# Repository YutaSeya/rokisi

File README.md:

# ロボトレーサー(仮名称ロキシ)

ロボトレース競技に参加するために製作したロボットの機体の設計データ、サンプルプログラムのリポジトリです。

仮名称のロキシは、ロボトレの基本を学ぶ車体の頭文字をとったものです。

## リポジトリの概要

このリポジトリのディレクトリ構成は以下のようになっています。

- Hardware
  - kicadのデータ等
  - 機械設計のデータ等
- firmware
  - Inc
  - Src
  - makefile
  - .gitignore
- LICENSE

# firmwareの使用方法について
1.makeやarm_none_eabi_gccのtoolchain等をインストールする。

Windows環境の開発環境の構築例: [PCの開発環境を整える(Windows10 WSL)](https://garberas.com/archives/38)

2. gitを使用してこのリポジトリをクローンする。
```bash
$git clone  
$cd 
```
3. このリポジトリのビルドを行う
```bash
$cd firmware/  
$make
```

初期プログラムでは、初期化関数だけ実行されます。Lチカを一度行い無限ループでなんの処理も行われません。
周辺機能を使用する時は、ファイルを確認していただければと思います。
また、モーターの回転方向等については、一意に決定することのできないため各自で書き換えていただければと思います。
該当する関数は、controlMotorです。

# hardwareについて
ハードウェアのファイルはkicadの回路設計データとモーターマウント等のSTL形式データが入っています。

使用しているモーターはドローンモーターのφ8.5mm,長さ20mmの8520モーター(7.4V)、ピニオンギアはkkpmoで購入した歯数20、モジュール0.3、穴径1.0mm、
スパーギアはMisumiのメカニカル加工部品の歯数80、モジュール0.3、穴径18.0mmです。

また、3DプリントデータはDMM.makeのアクリル(ウルトラ)で頼みました。AGILISTAを使用してみることを検討してもいいかもです。
MJFを頼みましたが、磁気式エンコーダを使うには精度が厳しいように感じました。

また、回路図、ハードウェアに複数問題点が見つかっているため、現在訂正中です。適宜データを最新版にアップしていく予定です。よろしくお願いいたします。

# その他
このリポジトリにはST MicroのLLAPIのソースコードが含まれています。

このリポジトリによって生じた問題等に責任は一切負いません。

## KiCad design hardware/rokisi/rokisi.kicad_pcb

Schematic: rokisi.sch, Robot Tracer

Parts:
C1, C3, C5, C15, C18: 10u; C_0603_HandSoldering
C2, C8, C10, C12, C17, C19, C20, C21, C22, C23, C24: 0.1u; C_0603_HandSoldering
C4, C6: 22u; C_0603_HandSoldering
C7: 100u; C_1206_HandSoldering
C9: 2.2u; C_0603_HandSoldering
C11: 1u; C_0603_HandSoldering
C13, C14: 100n; C_0603_HandSoldering
C16: 2.2uf; C_0603_HandSoldering
CN1: CONNECT; Pin_Header_Straight_1x02_Pitch2.54mm
CN2, CN3: CONNECT; Pin_Header_Straight_1x02_Pitch2.00mm
D1: LED; LED_0603_HandSoldering
D2: LATBT66B
D3, D4, D5, D6: LED; LED_0603_HandSoldering_silk
J1, J3, J6, J9: Conn_01x02_Female; enckiban_robotore_pad2
J2, J5, J7, J10: Conn_01x04_Female; enckiban_pad4
J4: Conn_01x13_Female; FFC-SMD_13P-P0.50_X05B20U13T
J8, J11: Conn_01x04_Female; Pin_Header_Straight_1x04_Pitch2.00mm
J12: Conn_01x03_Female; Pin_Header_Straight_1x03_Pitch2.54mm
Q1: SI2323DDS; SOT-23_Handsoldering
R2, R3, R8, R9, R12: 10k; R_0603_HandSoldering
R4, R5: 3.3k; R_0603_HandSoldering
R10, R11, R13, R14, R15, R16, R17: 1k; R_0603_HandSoldering
SW1: Tactsw; B3U-1000P
SW2, SW3: Tactsw; SKRPACE010
U1: SW_SPST; PCM12SMTR
U2: AZ1117-5.0; SOT-223
U3: AZ1086H-3.3; SOT-223
U4: CSTCE20M0V51-R0; CSTCE12M0G52A-R0_HandSolding
U7: tb6612; SSOP-24_5.3x8.2mm_Pitch0.65mm
U8: STM32F405RGT; LQFP-64_10x10mm_Pitch0.5mm
U9, U10: MA700; QFN-16_3x3mm_Pitch0.5mm
U11: MPU-6500; QFN-24_3x3mm_Pitch0.4mm_silk
U12: L3GD20

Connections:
+3V3: C1.2, C2.2, C6.1, C7.1, C8.2, C11.1, C12.1, C17.1, C19.2, C20.2, C22.1, C23.1, C24.2, D2.2, D3.2, D4.2, D5.2, D6.2, J4.1, J6.1, J8.1, J9.1, J11.1, SW2.1, SW3.1, U3.2, U3.4, U7.19, U7.20, U8.1, U8.13, U8.19, U8.32, U8.48, U8.64, U11.8, U11.13, U12.1
+5V: C4.1, C5.1, U2.2 (VO), U2.4, U3.3
+12V: C3.1, Q1.3 (D), R3.1, R4.1, U2.3 (VI), U7.13, U7.14, U7.24
AD0: J4.4, U8.26
AD1: J4.5, U8.25
AD2: J4.6, U8.24
AD3: J4.7, U8.23
AD4: J4.8, U8.22
AD5: J4.9, U8.21
AD6: J4.10, U8.20
AD7: J4.11, U8.17
AD8: J4.12, U8.16
AD9: J4.13, U8.15
AO1: CN2.1, U7.1, U7.2
AO2: CN2.2, U7.5, U7.6
BO1: CN3.1, U7.11, U7.12
BO2: CN3.2, U7.7, U7.8
GND: C1.1, C2.1, C3.2, C4.2, C5.2, C6.2, C7.2, C8.1, C9.1, C10.1, C11.2, C12.2, C16.2, C17.2, C19.1, C20.1, C21.2, C22.2, C23.2, C24.1, CN1.2, D1.1, J4.2, J4.3, J6.2, J8.2, J9.2, J11.2, J12.1, R5.2, R8.2, R9.1, R12.1, SW1.2, U1.2, U2.1 (GND), U3.1, U4.2, U7.3, U7.4, U7.9, U7.10, U7.18, U8.12, U8.18, U8.63, U11.11, U11.18, U11.20, U12.8
LEFT_CS: J2.1, U10.5
LEFT_GND: C14.2, C18.1, J1.2, U10.8
LEFT_MISO: J2.3, U10.7
LEFT_MOSI: J2.4, U10.4
LEFT_SCLK: J2.2, U10.12
LEFT_VDD: C14.1, J1.1, U10.13
unnamed: C9.2, U8.47
unnamed: C10.2, SW1.1, U8.7
unnamed: C15.2, U9.16
unnamed: C16.1, U8.31
unnamed: C18.2, U10.16
unnamed: C21.1, U11.10
unnamed: CN1.1, Q1.2 (S), R2.2
unnamed: D1.2, R4.2
unnamed: D2.1, R10.2
unnamed: D2.3, R11.1
unnamed: D2.4, R13.2
unnamed: D3.1, R14.1
unnamed: D4.1, R15.1
unnamed: D5.1, R16.1
unnamed: D6.1, R17.1
unnamed: Q1.1 (G), R2.1, U1.1
unnamed: R8.1, U8.28
unnamed: U4.1, U8.5
unnamed: U4.3, U8.6
RIGHT_CS: J5.1, U9.5
RIGHT_GND: C13.2, C15.1, J3.2, U9.8
RIGHT_MISO: J5.3, U9.7
RIGHT_MOSI: J5.4, U9.4
RIGHT_SCLK: J5.2, U9.12
RIGHT_VDD: C13.1, J3.1, U9.13
ad11: J8.3, U8.27
ad12: J11.3, U8.14
ain1: U7.21, U8.3
ain2: U7.22, U8.2
batt_analog: R3.2, R5.1, U8.9
bin1: U7.17, U8.4
bin2: U7.16, U8.8
boot: R12.2, SW3.2, U8.59, U8.60
fled_blue: R11.2, U8.44
fled_green: R13.1, U8.45
fled_red: R10.1, U8.46
gyro_clk: U8.51, U11.23, U12.2
gyro_miso: U8.52, U11.9, U12.4
gyro_mosi: U8.53, U11.24, U12.3
l3gd20_cs: U8.10, U12.5
led1: R14.2, U8.37
led2: R16.2, U8.38
led3: R15.2, U8.39
led4: R17.2, U8.40
led_left: J8.4, U8.41
led_right: J11.4, U8.29
mpu_cs: U8.11, U11.22
pushsw1: R9.2, SW2.2, U8.30
pwma: U7.23, U8.61
pwmb: U7.15, U8.62
spi1_clk: J7.2, U8.55
spi1_cs: J7.1, U8.54
spi1_miso: J7.3, U8.56
spi1_mosi: J7.4, U8.57
spi2_clk: J10.2, U8.34
spi2_cs: J10.1, U8.33
spi2_miso: J10.3, U8.35
spi2_mosi: J10.4, U8.36
usart1_rx: J12.2, U8.43
usart1_tx: J12.3, U8.42

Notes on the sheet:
Power
Gyro Sensor
PchMOSFET 20V5A
3-terminal regulator Input 6.25 to 20V OUTPUT 5V1A
3-terminal regulator Input 4.6 to 15V OUTPUT 3.3V1.5A
Motor Driver & Current IC
Encoder
MCU STM32F405RGT 64Pin
User Interface
Sensor Connect

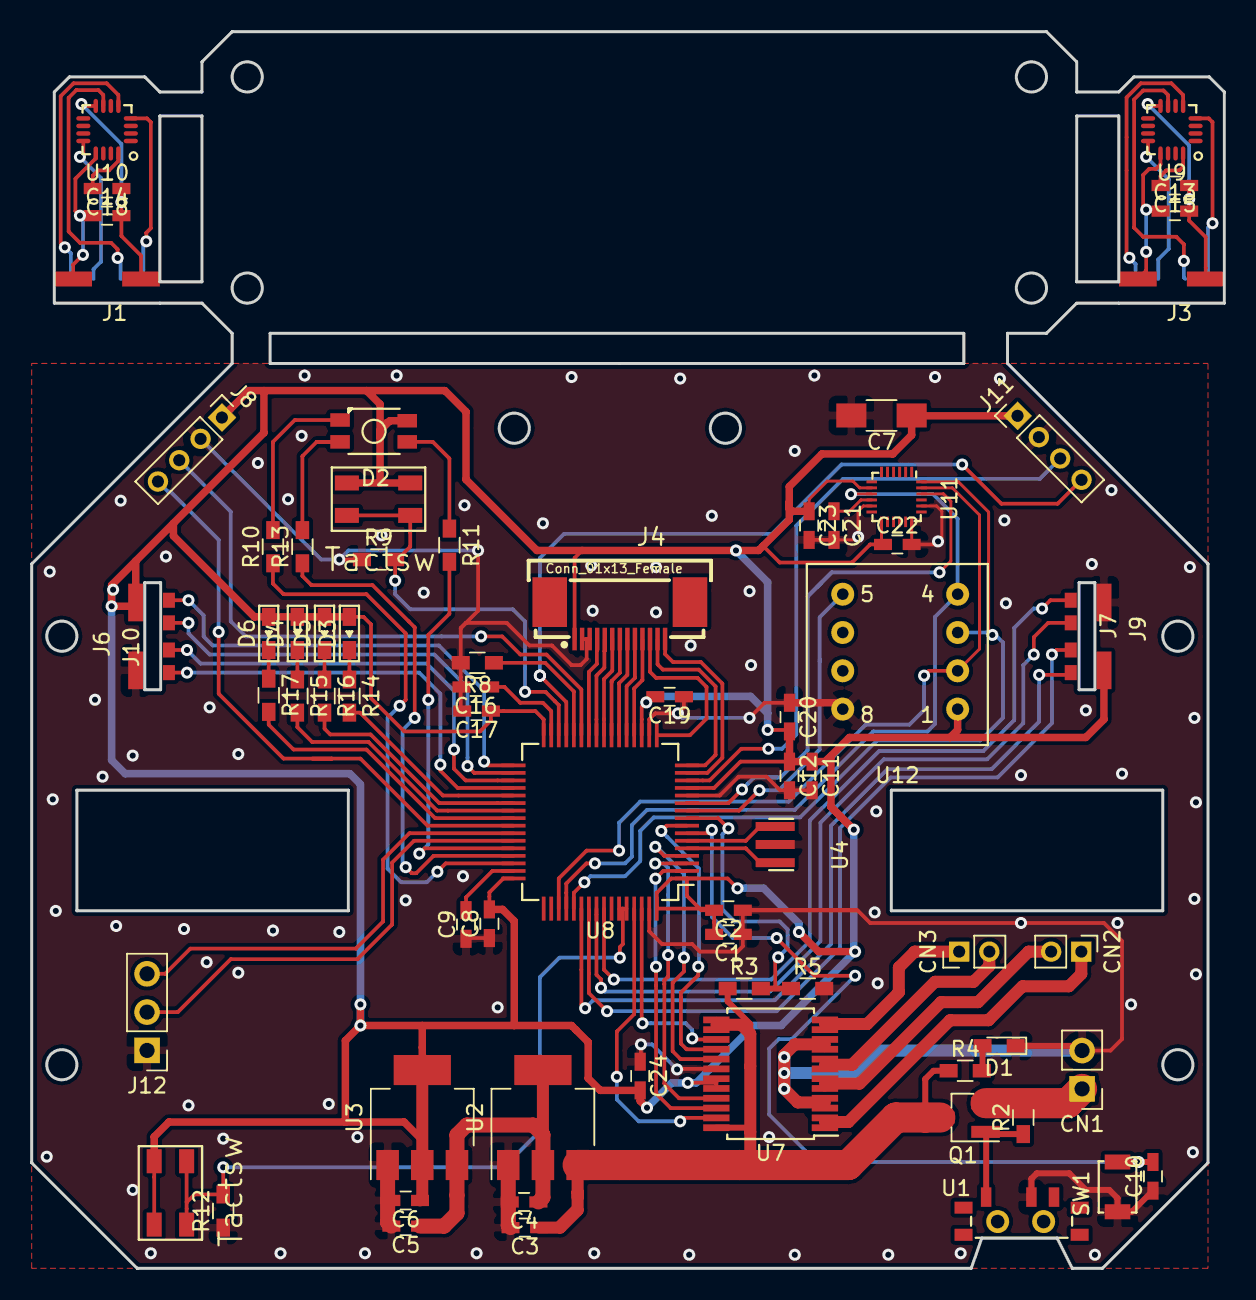
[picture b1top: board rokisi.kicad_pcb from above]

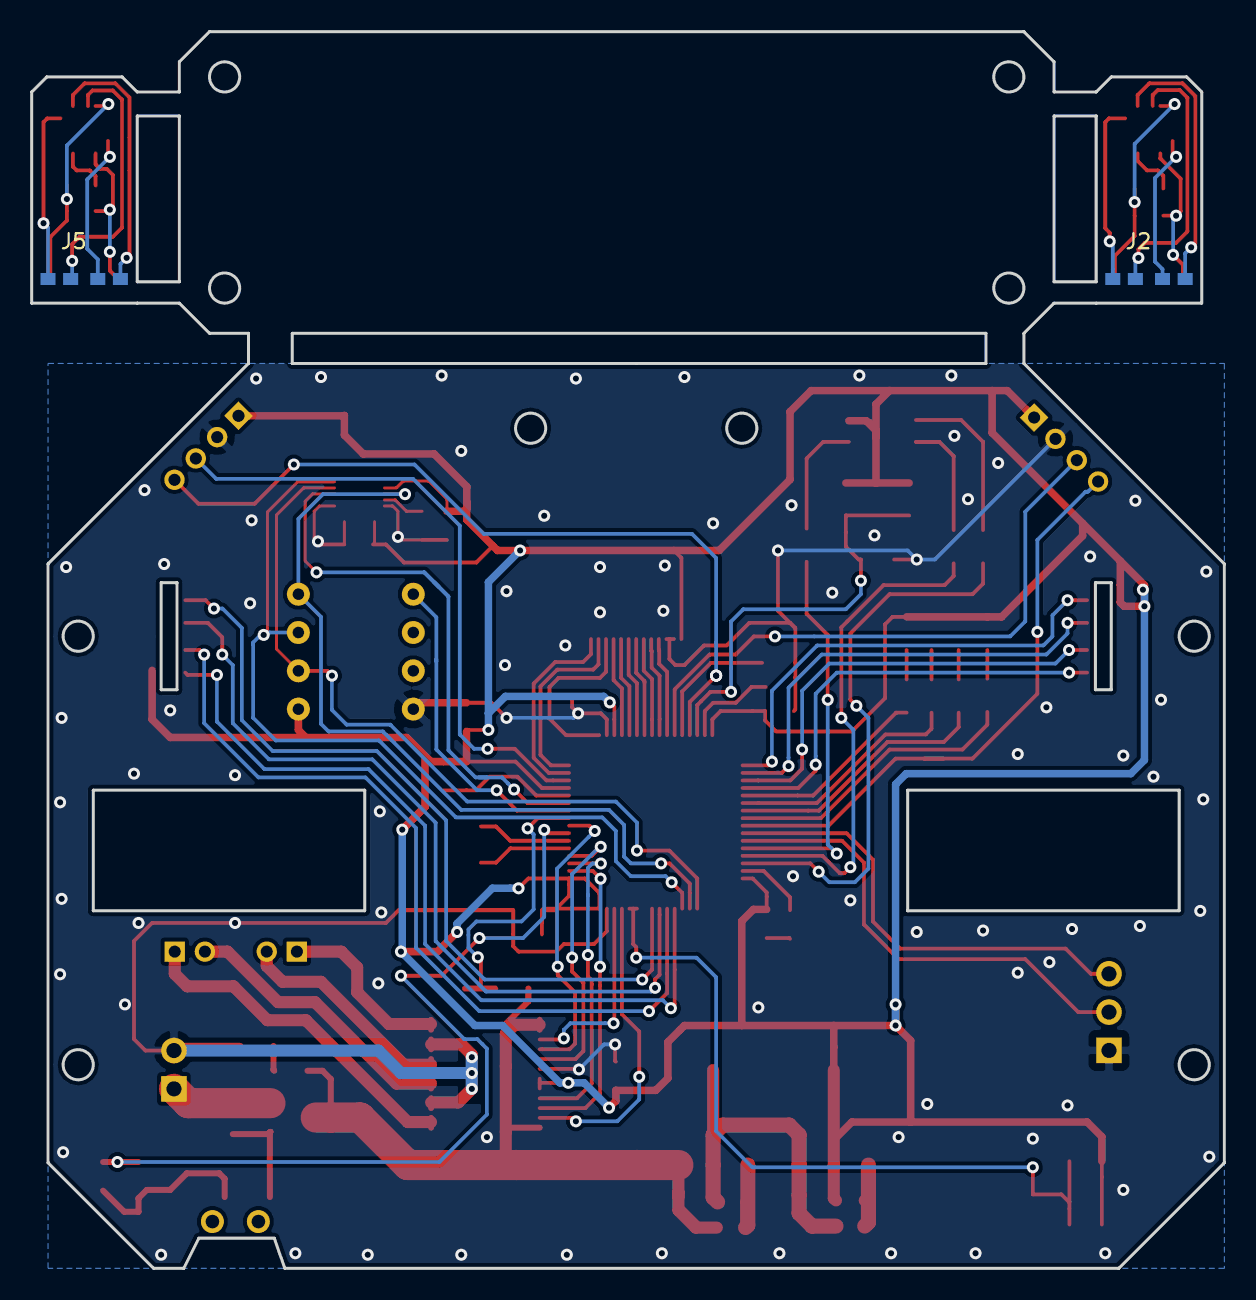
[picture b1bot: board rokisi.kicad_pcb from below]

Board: 2 copper layers, 79.1 x 82.0 mm, 73 parts (2 on the bottom side), 84 nets.

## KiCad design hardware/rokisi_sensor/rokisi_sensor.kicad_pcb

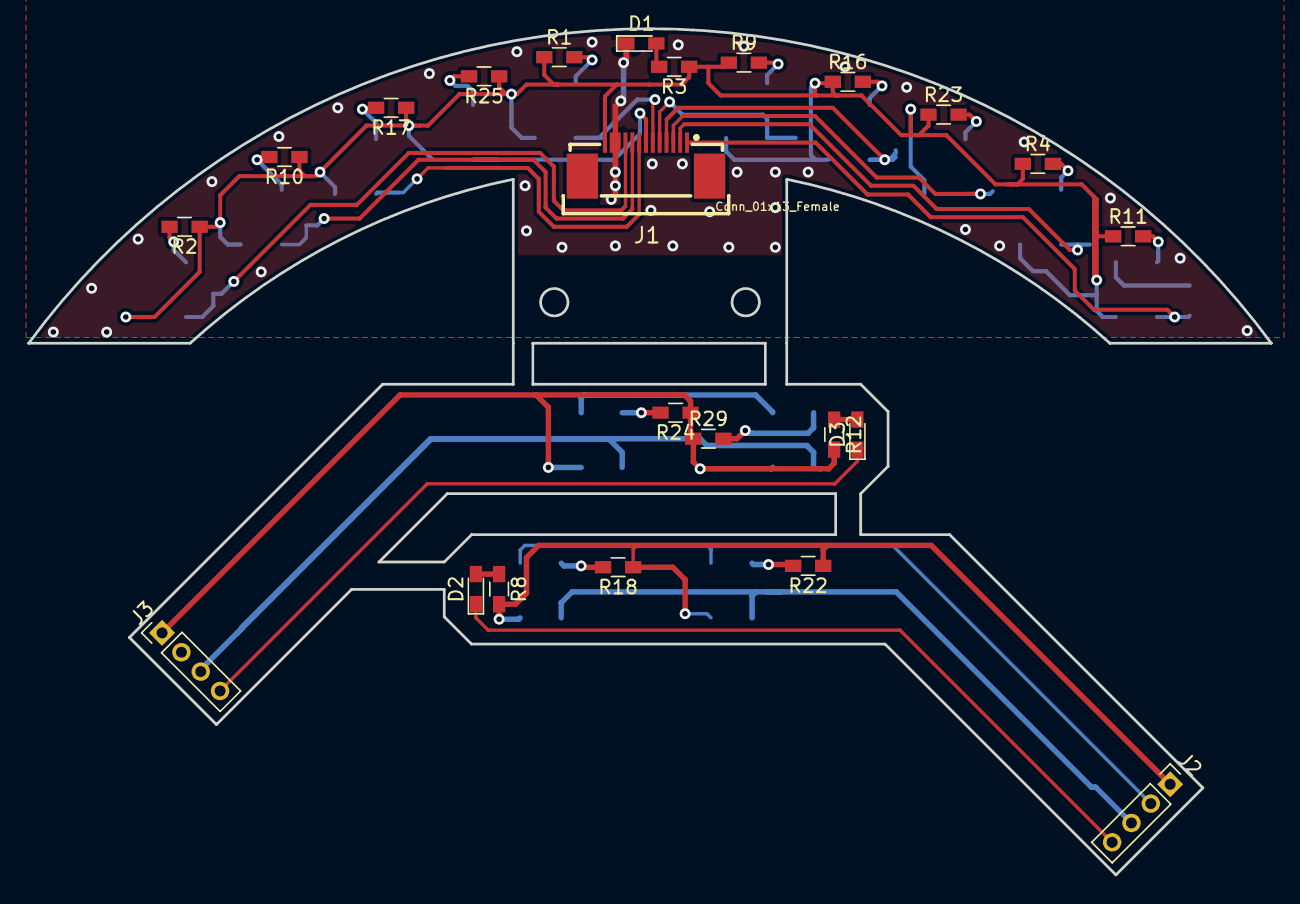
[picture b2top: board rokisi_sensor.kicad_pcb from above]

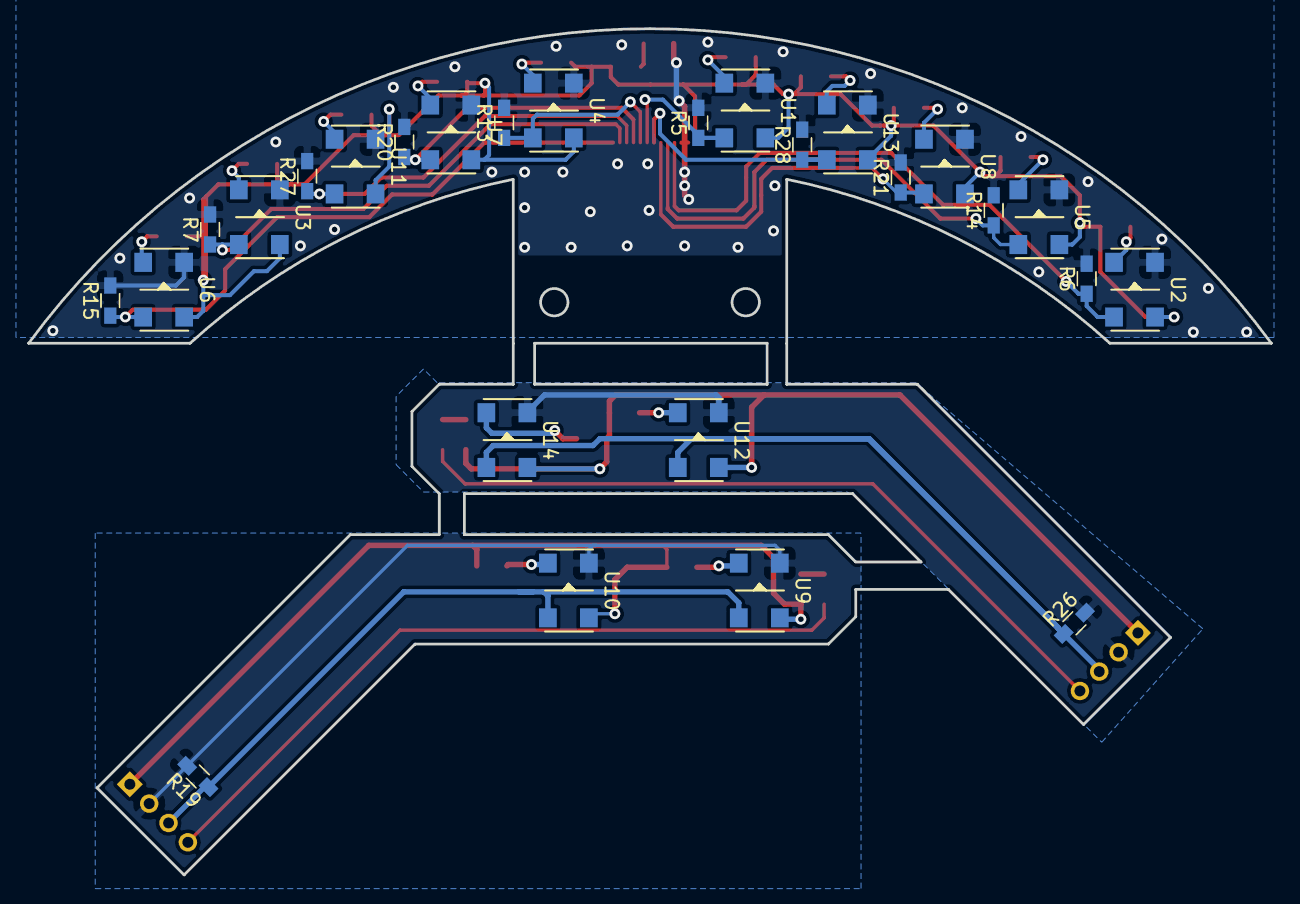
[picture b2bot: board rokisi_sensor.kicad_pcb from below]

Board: 2 copper layers, 90.9 x 61.9 mm, 49 parts (26 on the bottom side), 37 nets.

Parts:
D1, D2, D3: LED; LED_0603_HandSoldering
J1: Conn_01x13_Female; FFC-SMD_13P-P0.50_X05B20U13T
J2, J3: Conn_01x04_Female; Pin_Header_Straight_1x04_Pitch2.00mm
R1, R2, R4, R9, R10, R11, R16, R17, R18, R22, R23, R24, R25, R29: 330; R_0603_HandSoldering
R3, R5, R6, R7, R8, R12, R13, R14, R15, R19, R20, R21, R26, R27, R28: 1k; R_0603_HandSoldering
U1, U2, U3, U4, U5, U6, U7, U8, U9, U10, U11, U12, U13, U14: GP2S700HCP

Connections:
+3V3: J1.13, R1.1, R2.1, R3.1, R4.1, R9.1, R10.1, R11.1, R16.1, R17.1, R23.1, R25.1, U1.2, U2.2, U3.2, U4.2, U5.2, U6.2, U7.2, U8.2, U11.2, U13.2
AD0: J1.10, R6.1, U2.1
AD1: J1.9, R14.1, U5.1
AD2: J1.8, R21.1, U8.1
AD3: J1.7, R28.1, U13.1
AD4: J1.6, R5.1, U1.1
AD5: J1.5, R13.1, U4.1
AD6: J1.4, R20.1, U7.1
AD7: J1.3, R27.1, U11.1
AD8: J1.2, R7.1, U3.1
AD9: J1.1, R15.1, U6.1
GND: D1.1, J1.11, J1.12, R5.2, R6.2, R7.2, R13.2, R14.2, R15.2, R20.2, R21.2, R27.2, R28.2, U1.3, U2.3, U3.3, U4.3, U5.3, U6.3, U7.3, U8.3, U11.3, U13.3
LEFT_GND: J2.2, R19.2, U9.3, U10.3
LEFT_VCC: J2.1, R8.2, R18.1, R22.1, U9.2, U10.2
unnamed: D1.2, R3.2
unnamed: D2.2, R8.1
unnamed: D3.2, R12.1
unnamed: R1.2, U1.4
unnamed: R2.2, U2.4
unnamed: R4.2, U3.4
unnamed: R9.2, U4.4
unnamed: R10.2, U5.4
unnamed: R11.2, U6.4
unnamed: R16.2, U7.4
unnamed: R17.2, U8.4
unnamed: R18.2, U9.4
unnamed: R22.2, U10.4
unnamed: R23.2, U11.4
unnamed: R24.2, U12.4
unnamed: R25.2, U13.4
unnamed: R29.2, U14.4
RIGHT_GND: J3.2, R26.2, U12.3, U14.3
RIGHT_VCC: J3.1, R12.2, R24.1, R29.1, U12.2, U14.2
left_analog: J2.3, R19.1, U9.1, U10.1
left_led: D2.1, J2.4
right_analog: J3.3, R26.1, U12.1, U14.1
right_led: D3.1, J3.4

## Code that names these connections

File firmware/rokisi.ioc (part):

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Mcu.Name=STM32F405RGTx
Mcu.Package=LQFP64
Mcu.UserName=STM32F405RGTx
PA0-WKUP.Signal=ADCx_IN0
PA1.Signal=ADCx_IN1
PA10.Mode=Asynchronous
PA10.Signal=USART1_RX
PA11.GPIOParameters=GPIO_Label
PA11.GPIO_Label=fled_blue
PA11.Signal=GPIO_Output
PA12.GPIOParameters=GPIO_Label
PA12.GPIO_Label=fled_green
PA12.Signal=GPIO_Output
PA13.GPIOParameters=GPIO_Label
PA13.GPIO_Label=fled_red
PA13.Signal=GPIO_Output
PA2.GPIOParameters=GPIO_Label
PA2.GPIO_Label=led_right
PA2.Signal=GPIO_Output
PA3.GPIOParameters=GPIO_Label
PA3.GPIO_Label=fetb
PA3.Signal=GPIO_Output
PA4.Signal=ADCx_IN4
PA5.Signal=ADCx_IN5
PA6.Signal=ADCx_IN6
PA7.Signal=ADCx_IN7
PA8.GPIOParameters=GPIO_Label
PA8.GPIO_Label=fet_side_left
PA8.Signal=GPIO_Output
PA9.Mode=Asynchronous
PA9.Signal=USART1_TX
PB0.GPIOParameters=GPIO_Label
PB0.GPIO_Label=feta
PB0.Signal=GPIO_Output
PB1.Signal=ADCx_IN9
PB10.GPIOParameters=GPIO_Label
PB10.GPIO_Label=fet_side_right
PB10.Signal=GPIO_Output
PB11.GPIOParameters=GPIO_Label
PB11.GPIO_Label=pushsw1
PB11.Signal=GPIO_Input
PB12.GPIOParameters=GPIO_Label
PB12.GPIO_Label=enc_left_cs
PB12.Signal=GPIO_Output
PB13.Mode=Full_Duplex_Master
PB13.Signal=SPI2_SCK
PB14.Mode=Full_Duplex_Master
PB14.Signal=SPI2_MISO
PB15.Mode=Full_Duplex_Master
PB15.Signal=SPI2_MOSI
PB3.Mode=Full_Duplex_Master
PB3.Signal=SPI1_SCK
PB4.Mode=Full_Duplex_Master
PB4.Signal=SPI1_MISO
PB5.Mode=Full_Duplex_Master
PB5.Signal=SPI1_MOSI
PB7.GPIOParameters=GPIO_Label
PB7.GPIO_Label=pushsw2
PB7.Signal=GPIO_Input
PB8.Signal=S_TIM4_CH3
PB9.Signal=S_TIM4_CH4
PC0.GPIOParameters=GPIO_Label
PC0.GPIO_Label=bin2
PC0.Signal=GPIO_Output
PC1.Signal=ADCx_IN11
PC10.Mode=Full_Duplex_Master
PC10.Signal=SPI3_SCK
PC11.Mode=Full_Duplex_Master
PC11.Signal=SPI3_MISO
PC12.Mode=Full_Duplex_Master
PC12.Signal=SPI3_MOSI
PC13-ANTI_TAMP.GPIOParameters=GPIO_Label
PC13-ANTI_TAMP.GPIO_Label=ain2
PC13-ANTI_TAMP.Signal=GPIO_Output
PC14-OSC32_IN.GPIOParameters=GPIO_Label
PC14-OSC32_IN.GPIO_Label=ain1
PC14-OSC32_IN.Signal=GPIO_Output
PC15-OSC32_OUT.GPIOParameters=GPIO_Label
PC15-OSC32_OUT.GPIO_Label=bin1
PC15-OSC32_OUT.Signal=GPIO_Output
PC2.GPIOParameters=GPIO_Label
PC2.GPIO_Label=l3gd20_cs
PC2.Signal=GPIO_Output
PC3.GPIOParameters=GPIO_Label
PC3.GPIO_Label=mpu_cs
PC3.Signal=GPIO_Output
PC4.Signal=ADCx_IN14
PC5.GPIOParameters=GPIO_Label
PC5.GPIO_Label=led_left
PC5.Signal=GPIO_Output
PC6.GPIOParameters=GPIO_Label
PC6.GPIO_Label=led1
PC6.Signal=GPIO_Output
PC7.GPIOParameters=GPIO_Label
PC7.GPIO_Label=led2
PC7.Signal=GPIO_Output
PC8.GPIOParameters=GPIO_Label
PC8.GPIO_Label=led3
PC8.Signal=GPIO_Output
PC9.GPIOParameters=GPIO_Label
PC9.GPIO_Label=led4
PC9.Signal=GPIO_Output
PD2.GPIOParameters=GPIO_Label
PD2.GPIO_Label=enc_right_cs
PD2.Signal=GPIO_Output
PH0-OSC_IN.Mode=HSE-External-Oscillator
PH0-OSC_IN.Signal=RCC_OSC_IN
PH1-OSC_OUT.Mode=HSE-External-Oscillator
PH1-OSC_OUT.Signal=RCC_OSC_OUT
RCC.HSE_VALUE=20000000
RCC.SYSCLKFreq_VALUE=160000000
RCC.SYSCLKSource=RCC_SYSCLKSOURCE_PLLCLK
board=custom

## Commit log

2020-04-18 init commit
2020-04-19 Correct the mistake(DMA2_Stream0_IRQHandler)
2020-04-21 update readme and 3D data
2020-04-23 misstake Logic inversion
2020-05-23 update program
